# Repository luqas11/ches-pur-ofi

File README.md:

# ches-pur-ofi

### What is this
This project is the **firmware** and **PCB design** for the hardware interface between the [Sega Model 2](https://emulation.gametechwiki.com/index.php/Sega_Model_2) emulator and **a custom homemade cockpit** which has two **pedals**, a **steering wheel**, an **H shifter** and an **analog speedometer**. The idea is to play [Daytona USA](https://en.wikipedia.org/wiki/Daytona_USA) on the emulator while using the cockpit controls and to keep the speedometer pointer in sync with the game car speed. An [Arduino Leonardo](https://docs.arduino.cc/hardware/leonardo) board makes this interface possible, reading the input values and sending them to the PC as PC Joysick buttons and axes. Also, the board controls the servo that drives the speedometer pointer and processes the car speed value given by the emulator. A custom PCB design simplifies the setup process, allowing the user to just plug the *Leonardo* into the PCB and play, without additional wiring.  

The repo has the following project components:
- A **LUA script** that runs in the emulator and broadcasts the car speed value to the *Leonardo*
- A **C++ sketch** that is the firmware running inside the *Leonardo*, which processes the controls inputs and the speedometer motor output
- A **custom PCB** that has some pins to simplify the electrical connections between the *Leonardo* and the cockpit potentiometers and buttons

### How to use it
While in the cockpit, plug the *Leonardo* to the board and the USB to the PC. Run the emulator from the `Daytona USA.bat` script, and specify the *Leonardo* COM port number when asked to. After that, the game shuld start with all the controls operational. Axes calibration process is explained in the `firmware` readme file, and is usually needed after a hardware change (i.e. after replacing potentiometers). In the top left corner an informative text shows the port connection status, and it's behavior is also explained in the `firmware` readme.

### Some screenshots
#### Gameplay with a successful connection to the *Leonardo* (notice the top-left corner text displaying the COM port name in green):

#### Gameplay with the connection to the *Leonardo* lost (notice the top-left corner text displaying the COM port name in red):

#### PCB layout:

#### PCB 3D model:

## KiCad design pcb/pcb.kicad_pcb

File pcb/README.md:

# PCB

This is a PCB design that simplifies physical wiring between the cockpit controls and the *Leonardo*. The circuit schematic and the PCB layout are printed in the `pcb-schematic.pdf` and `pcb-layout.pdf` files respectively. The 3D support model is a printable part that allows a solid attachment of the PCB to the cockpit structure.

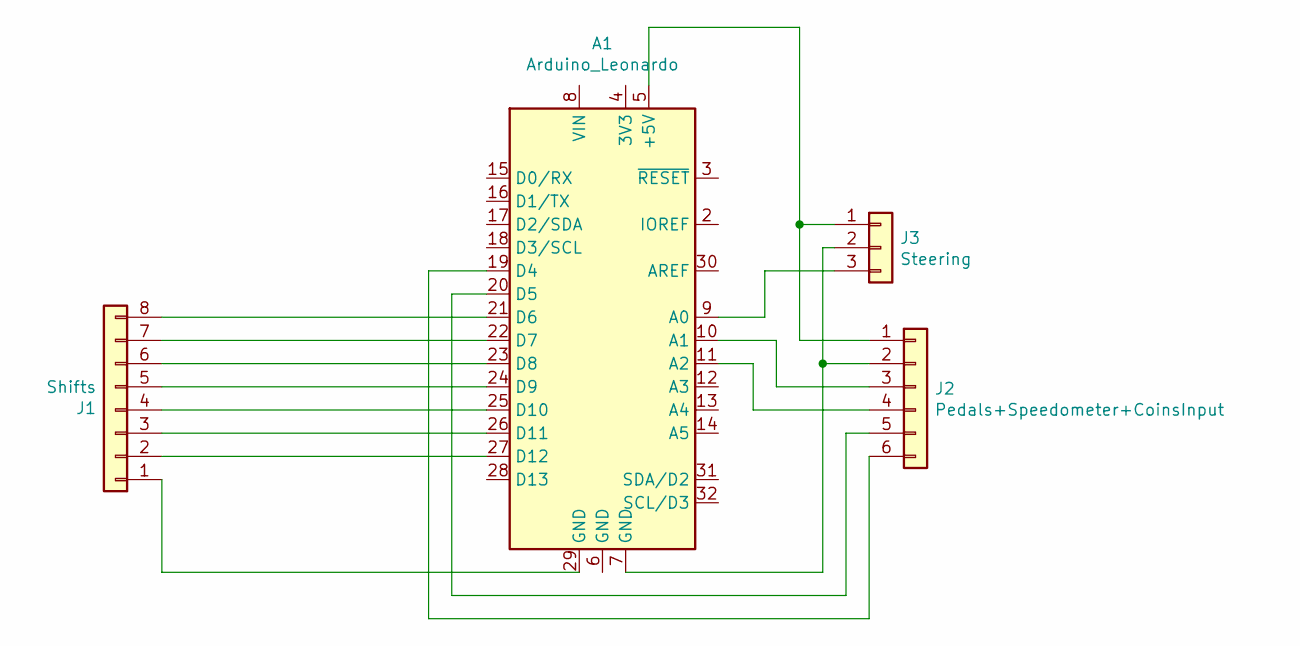
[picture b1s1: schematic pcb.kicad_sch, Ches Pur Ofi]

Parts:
A1: Arduino_Leonardo
J1: Shifts; PinSocket_1x08_P2.54mm_Vertical
J2: Pedals+Speedometer+CoinsInput; PinSocket_1x06_P2.54mm_Vertical
J3: Steering; PinSocket_1x03_P2.54mm_Vertical

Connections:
unnamed: A1.5 (+5V), J2.1, J3.1
unnamed: A1.9 (A0), J3.3
unnamed: A1.10 (A1), J2.3
unnamed: A1.11 (A2), J2.4
unnamed: A1.19 (D4), J2.6
unnamed: A1.20 (D5), J2.5
unnamed: A1.21 (D6), J1.8
unnamed: A1.22 (D7), J1.7
unnamed: A1.23 (D8), J1.6
unnamed: A1.24 (D9), J1.5
unnamed: A1.25 (D10), J1.4
unnamed: A1.26 (D11), J1.3
unnamed: A1.27 (D12), J1.2
unnamed: A1.29 (GND), J1.1
unnamed: A1.7 (GND), J2.2, J3.2

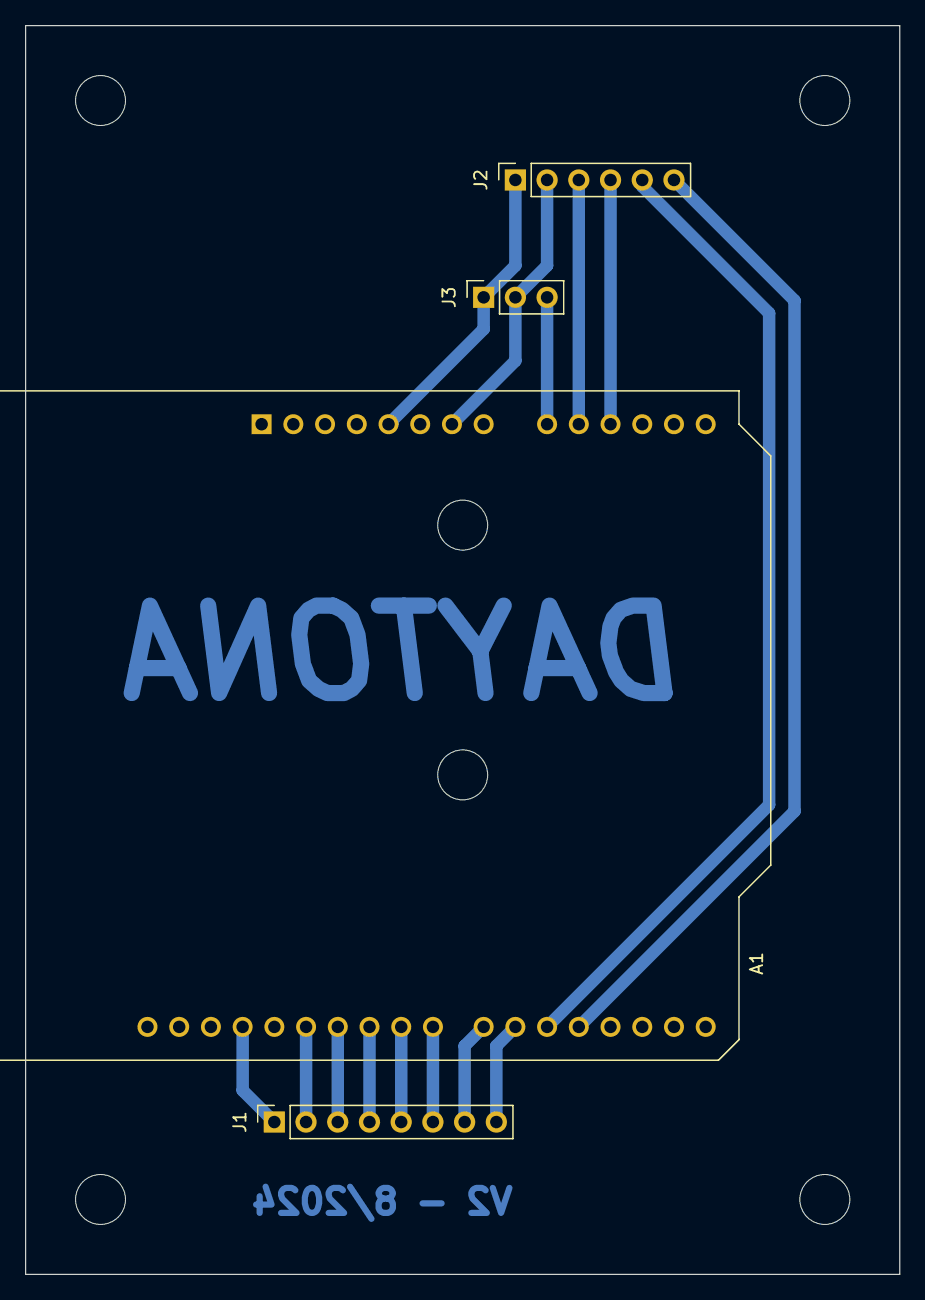
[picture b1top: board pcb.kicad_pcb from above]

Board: 2 copper layers, 70.0 x 100.0 mm, 4 parts (0 on the bottom side), 15 nets.

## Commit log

2023-12-31 Add first project version
2023-12-31 Rename Daytona.ino to firmware.ino
2023-12-31 Fix calibration value
2023-12-31 Remove Arduino Joystick Library copy
2024-01-02 Rename and update KiCad project
2024-01-03 Add layout and schematic prints
2024-01-03 Fix schematic wording
2024-01-03 Add PCB and gameplay screenshots
2024-02-11 Update game records
2024-02-11 Change footprints folder name
2024-02-11 Fix footprints folder name
2024-08-05 Add new PCB support and update PCB layout
2024-08-05 Reduce PCB support height
2024-08-14 Update PCB support to avoid component collision
2024-08-14 Add new screenshots and PCB layout print
2024-12-24 Remove VSCode Arduino extension configuration files
2024-12-24 Format firware sketch with the Arduino IDE 2 auto formatter
2024-12-31 Calibrate analog input
2024-12-31 Revert "Calibrate analog input"
    This reverts commit f309faef71e151e480f45b0960043010463a14e1.
2025-02-10 Add servo offset to speedometer value calculation
2026-02-01 Calibrate analog input and update game records
